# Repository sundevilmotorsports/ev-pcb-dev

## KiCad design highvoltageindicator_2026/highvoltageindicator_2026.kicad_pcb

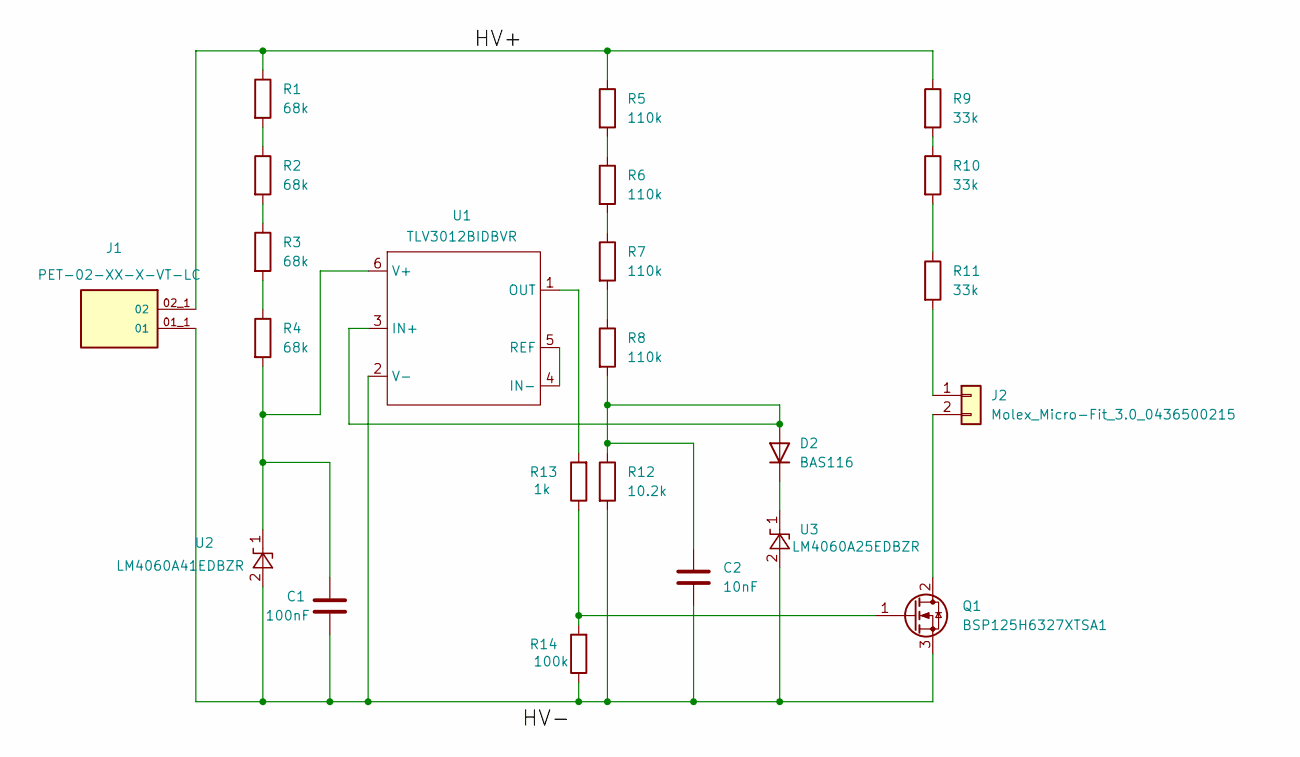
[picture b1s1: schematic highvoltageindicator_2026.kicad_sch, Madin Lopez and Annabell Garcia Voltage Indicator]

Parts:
C1: 100nF; C_1206_3216Metric
C2: 10nF; C_1206_3216Metric
D2: BAS116; SOT-23
J1: PET-02-XX-X-VT-LC; SAMTEC_PET-02-XX-X-VT-LC; PARTREV C
J2: Molex_Micro-Fit_3.0_0436500215; Molex_Micro-Fit_3.0_43650-0215_1x02_P3.00mm_Vertical
Q1: BSP125H6327XTSA1; SOT-223-3_TabPin2
R1, R2, R3, R4: 68k; R_2512_6332Metric
R5, R6, R7, R8: 110k; R_1206_3216Metric
R9, R10, R11: 33k; R_2512_6332Metric
R12: 10.2k; R_1206_3216Metric
R13: 1k; R_1206_3216Metric
R14: 100k; R_1206_3216Metric
U1: TLV3012BIDBVR; SOT-23-6
U2: LM4060A41EDBZR; SOT-23
U3: LM4060A25EDBZR; SOT-23

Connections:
/HV+: J1.02_1 (02), R1.1, R5.1, R9.1
unnamed: C2.1, D2.2 (A), R8.2, R12.1, U1.3 (IN+)
unnamed: D2.1 (K), U3.1 (K)
unnamed: C1.2, C2.2, J1.01_1 (01), Q1.3 (S), R12.2, R14.1, U1.2 (V-), U2.2 (A), U3.2 (A)
unnamed: J2.1, R11.2
unnamed: J2.2, Q1.2 (D)
unnamed: Q1.1 (G), R13.1, R14.2
unnamed: R1.2, R2.1
unnamed: R2.2, R3.1
unnamed: R3.2, R4.1
unnamed: R5.2, R6.1
unnamed: R6.2, R7.1
unnamed: R7.2, R8.1
unnamed: R9.2, R10.1
unnamed: R10.2, R11.1
unnamed: U1.4 (IN-), U1.5 (REF)
unnamed: R13.2, U1.1 (OUT)
unnamed: C1.1, R4.2, U1.6 (V+), U2.1 (K)

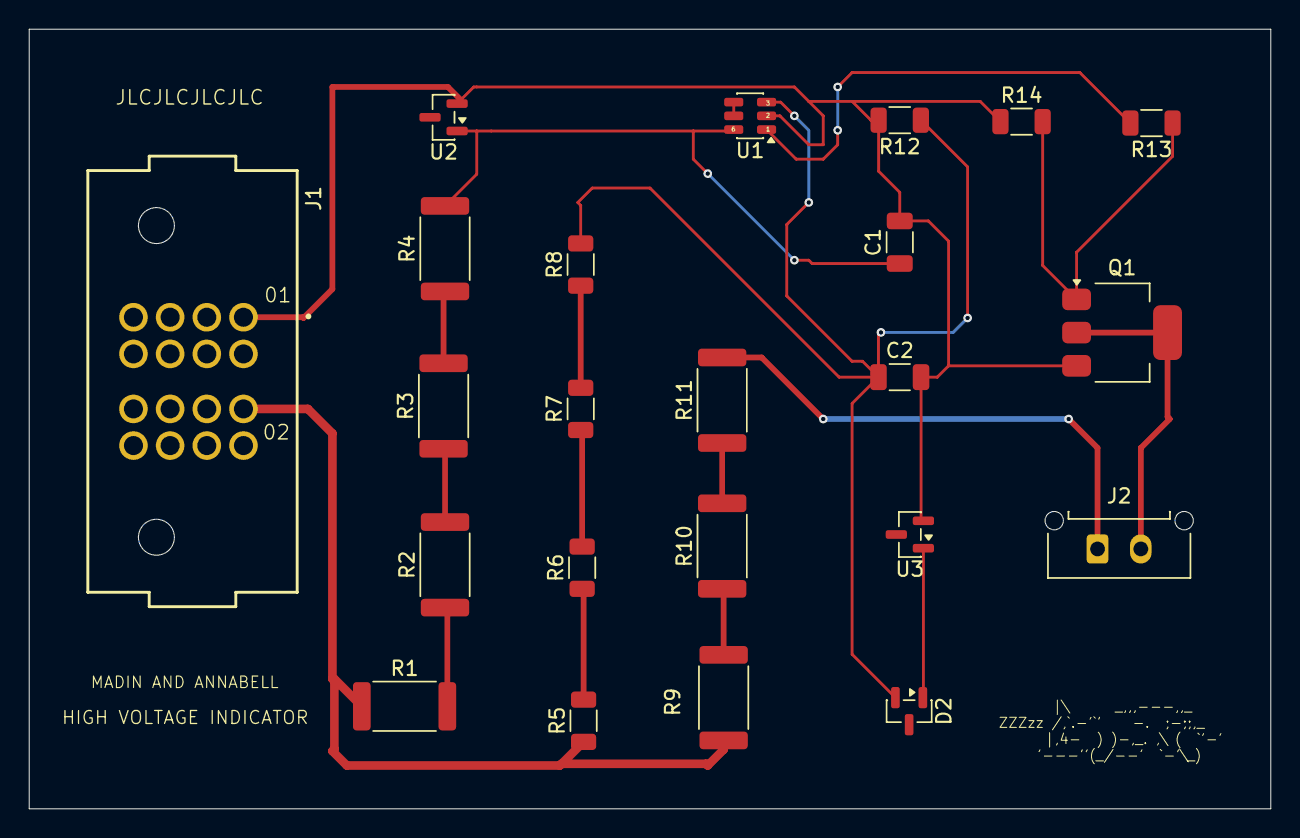
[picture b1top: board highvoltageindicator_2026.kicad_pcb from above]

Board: 4 copper layers, 86.0 x 54.0 mm, 23 parts (0 on the bottom side), 18 nets.

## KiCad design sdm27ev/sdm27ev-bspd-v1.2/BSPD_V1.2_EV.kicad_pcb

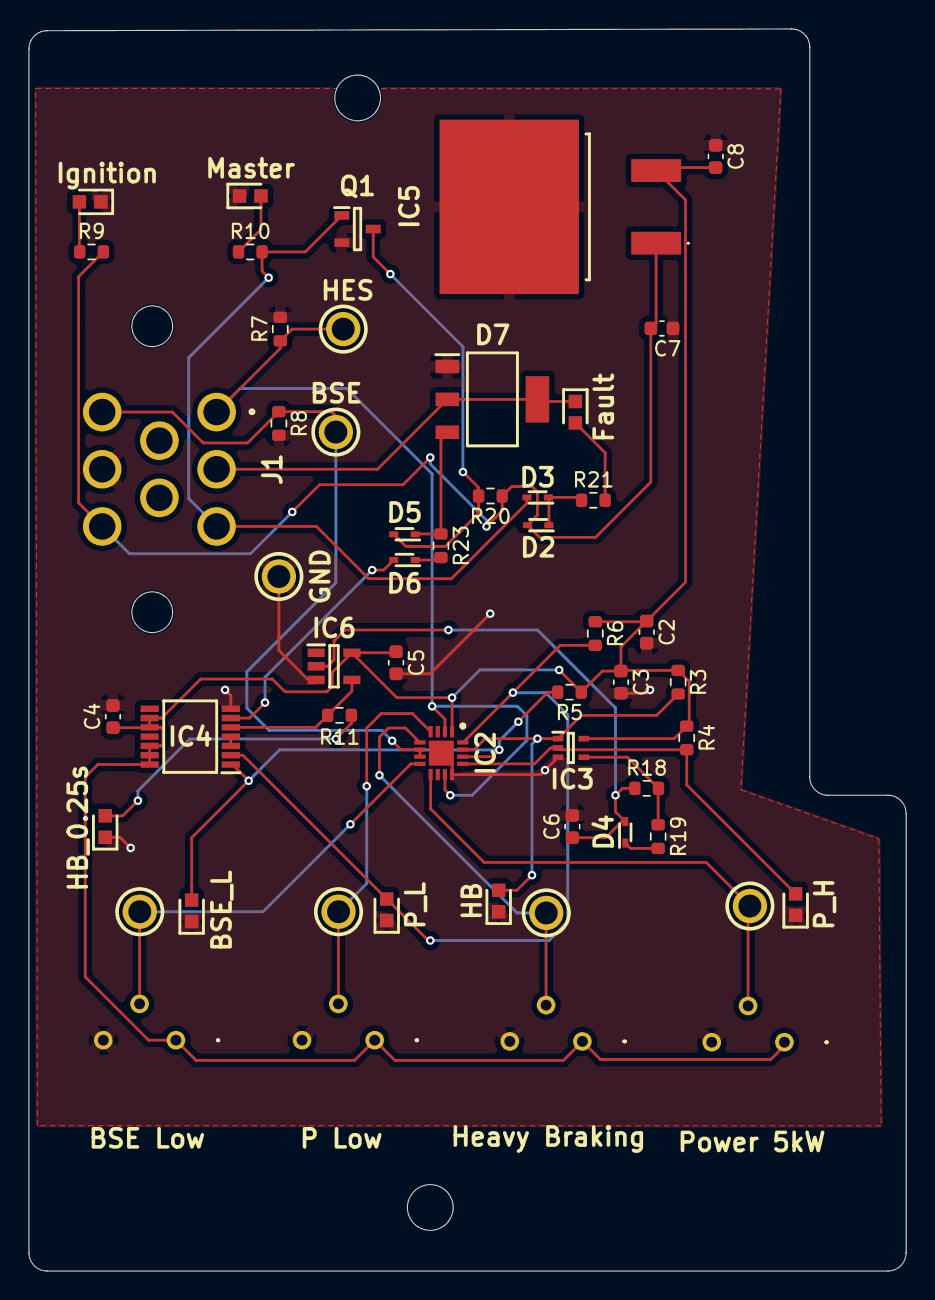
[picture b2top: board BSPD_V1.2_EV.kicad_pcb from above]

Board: 2 copper layers, 61.3 x 86.9 mm, 53 parts (0 on the bottom side), 29 nets.

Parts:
BLACK_TP1: 5006
BSE_L: 150060GS75000; LEDC1608X80N
C2, C3, C4, C5: 1uF; C_0603_1608Metric
C6: 10uF; C_0603_1608Metric
C7: 0.33uF; C_0603_1608Metric
C8: 0.1uF; C_0603_1608Metric
D2, D3, D4, D5, D6: BAT54XV2T1G; SODFL1608X70N
D7: X0202MN_5BA4; SOT230P700X190-4N
Fault: 150060GS75000; LEDC1608X80N
HB: 150060GS75000; LEDC1608X80N
HB_0.25s: 150060GS75000; LEDC1608X80N
IC2: LM2901BIRTER; QFN50P300X300X80-17N-D
IC3: 74AHC1G08; SOT65P212X110-5L
IC4: SN74HC32PWR; SOP65P640X120-14L
IC5: L7805ACD2T-TR; L7805ACD2TTR
IC6: SN74LVC1G17DBVRG4; SOT95P280X145-5N
Ignition: 150060RS75000; LEDC1608X80N
J1: 776280-1
Master: 150060RS75000; LEDC1608X80N
P_H: 150060GS75000; LEDC1608X80N
P_L: 150060GS75000; LEDC1608X80N
Q1: 2N7002,215; SOT95P230X110-3N
R3, R4, R5, R6, R11: 220; R_0603_1608Metric
R7, R8, R20: 10k; R_0603_1608Metric
R9, R10, R21: 510; R_0603_1608Metric
R18: 25k; R_0603_1608Metric
R19: 100; R_0603_1608Metric
R23: 1k; R_0603_1608Metric
RED_TP3, RED_TP4, RED_TP5, RED_TP6: 5005
VR3, VR4, VR5, VR6: 10k; 3386P1103TLF
WHITE_TP1, WHITE_TP2: 5007

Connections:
+5V: C2.1, C3.1, C4.1, C5.1, C8.2, IC2.1 (VCC), IC3.5 (VCC), IC4.9 (3A), IC4.10 (3B), IC4.12 (4A), IC4.13 (4B), IC4.14 (VCC), IC5.3 (OUT), IC6.5 (VCC), R3.1, R4.1, R5.1, R6.1, VR3.1 (CCW), VR4.1 (CCW), VR5.1 (CCW), VR6.1 (CCW)
/12V IGNITION: C7.2, D2.2 (A), IC5.1 (IN), J1.8, R9.2, R20.1
/12V MASTER: D3.2 (A), J1.3, Q1.1 (G), R10.2
/BL+PL_FAULT: IC4.3 (1Y), IC4.4 (2A)
/BSE: IC2.6 (IN2+), IC2.7 (IN3-), J1.6, R8.1, WHITE_TP1.1
/BSE_LOW_FAULT: BSE_L.2 (A), IC2.14 (OUT3), IC4.1 (1A), R5.2
/BSE_LOW_REF: IC2.8 (IN3+), RED_TP6.1, VR6.2 (Wiper)
/BSPD_LOGIC_SIGNAL: D6.2 (A), IC4.6 (2Y)
/HB*5kW_0.25s_FAULT: IC4.5 (2B), IC6.4 (Y), R11.1
/HB*5kW_FAULT: C6.1, D4.2 (A), IC6.2 (A), R18.2
/HEAVY_BRAKING_FAULT: HB.2 (A), IC2.15 (OUT2), IC3.1 (B), R3.2
/HEAVY_BRAKING_REF: IC2.5 (IN2-), RED_TP4.1, VR4.2 (Wiper)
/P_5kW_FAULT: IC2.13 (OUT4), IC3.2 (A), P_H.2 (A), R4.2
/P_HIGH_REF: IC2.9 (IN4-), RED_TP3.1, VR3.2 (Wiper)
/P_LOW_FAULT: IC2.16 (OUT1), IC4.2 (1B), P_L.2 (A), R6.2
/P_LOW_REF: IC2.4 (IN1+), RED_TP5.1, VR5.2 (Wiper)
/P_MAIN: IC2.2 (IN1-), IC2.11 (IN4+), J1.1, R7.1, WHITE_TP2.1
/SCR Gate: D5.1 (K), D7.3 (G), R23.1
BSPD KILL SIGNAL: D7.2 (A_1), D7.4 (A_2), Fault.1 (K), J1.2
GND: BLACK_TP1.1, BSE_L.1 (K), C2.2, C3.2, C4.2, C5.2, C6.2, C7.1, C8.1, D7.1 (K), HB.1 (K), HB_0.25s.1 (K), IC2.12 (GND), IC2.17 (EP), IC3.3 (GND), IC4.7 (GND), IC5.2 (GND), IC6.3 (GND), Ignition.1 (K), J1.7, Master.1 (K), P_H.1 (K), P_L.1 (K), Q1.2 (S), R7.2, R8.2, VR3.3 (CW), VR4.3 (CW), VR5.3 (CW), VR6.3 (CW)
unnamed: D2.1 (K), D3.1 (K), R21.1
unnamed: D4.1 (K), R19.2
unnamed: D5.2 (A), Q1.3 (D), R20.2
unnamed: D6.1 (K), R23.2
unnamed: IC3.4 (Y), R18.1, R19.1
unnamed: Ignition.2 (A), R9.1
unnamed: Master.2 (A), R10.1
unnamed: Fault.2 (A), R21.2
unnamed: HB_0.25s.2 (A), R11.2

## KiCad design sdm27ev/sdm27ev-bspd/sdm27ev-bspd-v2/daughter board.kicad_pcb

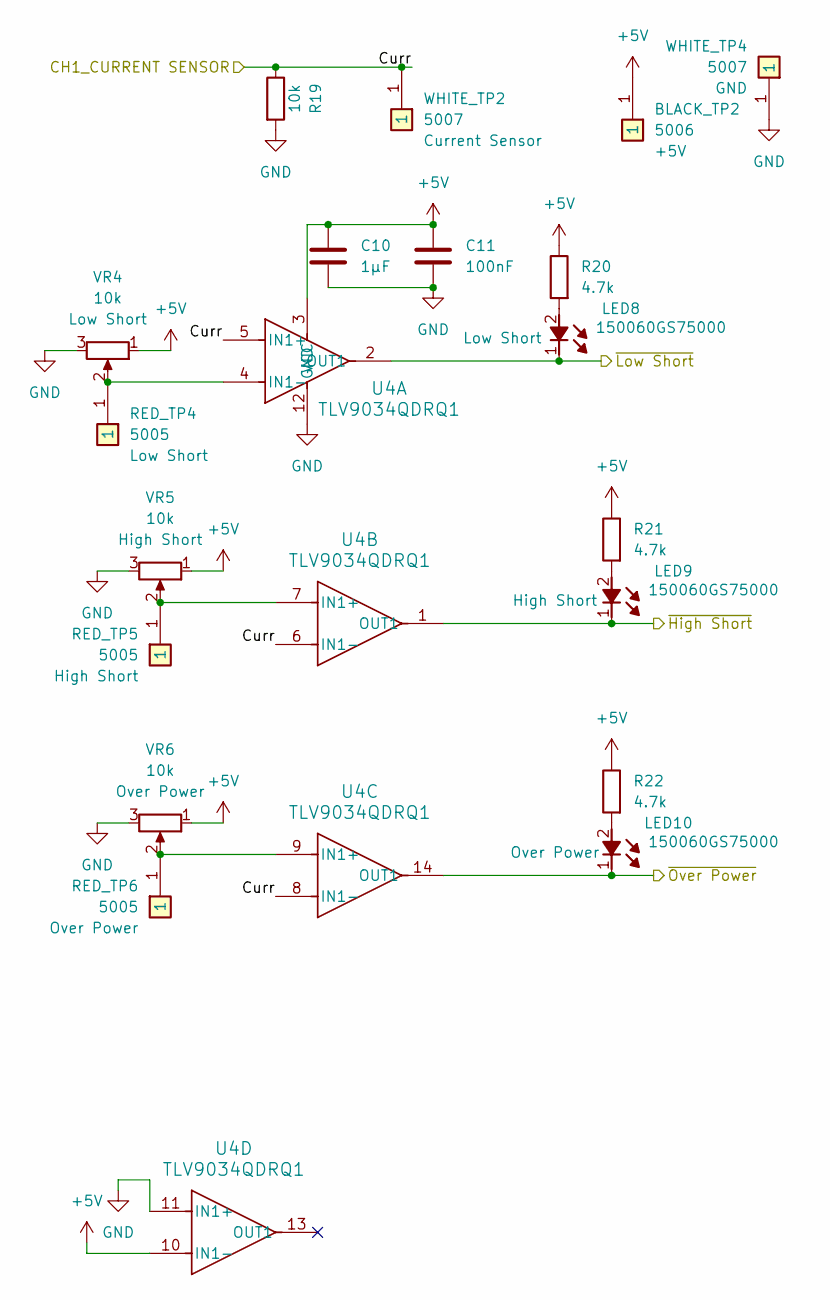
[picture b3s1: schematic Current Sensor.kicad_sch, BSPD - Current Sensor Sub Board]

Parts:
BLACK_TP2: 5006; Mouser Part Number 534-5006
C10: 1µF; C_0603_1608Metric
C11: 100nF; C_0603_1608Metric
LED8, LED9, LED10: 150060GS75000; LEDC1608X80N; Mouser Part Number 710-150060GS75000
R19: 10k; R_0603_1608Metric
R20, R21, R22: 4.7k; R_0603_1608Metric
RED_TP4, RED_TP5, RED_TP6: 5005; Mouser Part Number 534-5005
U4: TLV9034QDRQ1; SOIC-14_3.9x8.7mm_P1.27mm; Manufacturer_Part_Number TLV9034QDRQ1; Mouser Part Number 595-TLV9034QDRQ1
VR4, VR5, VR6: 10k; 3386P1103TLF; Mouser Part Number 652-3386P-1-103TLF
WHITE_TP2, WHITE_TP4: 5007; Mouser Part Number 534-5007

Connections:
+5V: BLACK_TP2.1 (1_1), C10.1, C11.1, R20.1, R21.1, R22.1, U4.3 (VCC), U4.10 (IN1-), VR4.1 (CCW), VR5.1 (CCW), VR6.1 (CCW); also elsewhere on the board
/CH1_CURRENT SENSOR: R19.1, U4.5 (IN1+), U4.6 (IN1-), U4.8 (IN1-), WHITE_TP2.1 (1_1); also elsewhere on the board
/~High Short: LED9.1 (K), U4.1 (OUT1); also elsewhere on the board
/~Low Short: LED8.1 (K), U4.2 (OUT1); also elsewhere on the board
/~Over Power: LED10.1 (K), U4.14 (OUT1); also elsewhere on the board
GND: C10.2, C11.2, R19.2, U4.11 (IN1+), U4.12 (GND), VR4.3 (CW), VR5.3 (CW), VR6.3 (CW), WHITE_TP4.1 (1_1); also elsewhere on the board
unnamed: LED8.2 (A), R20.2
unnamed: LED9.2 (A), R21.2
unnamed: LED10.2 (A), R22.2
unnamed: RED_TP4.1 (1_1), U4.4 (IN1-), VR4.2 (Wiper)
unnamed: RED_TP5.1 (1_1), U4.7 (IN1+), VR5.2 (Wiper)
unnamed: RED_TP6.1 (1_1), U4.9 (IN1+), VR6.2 (Wiper)

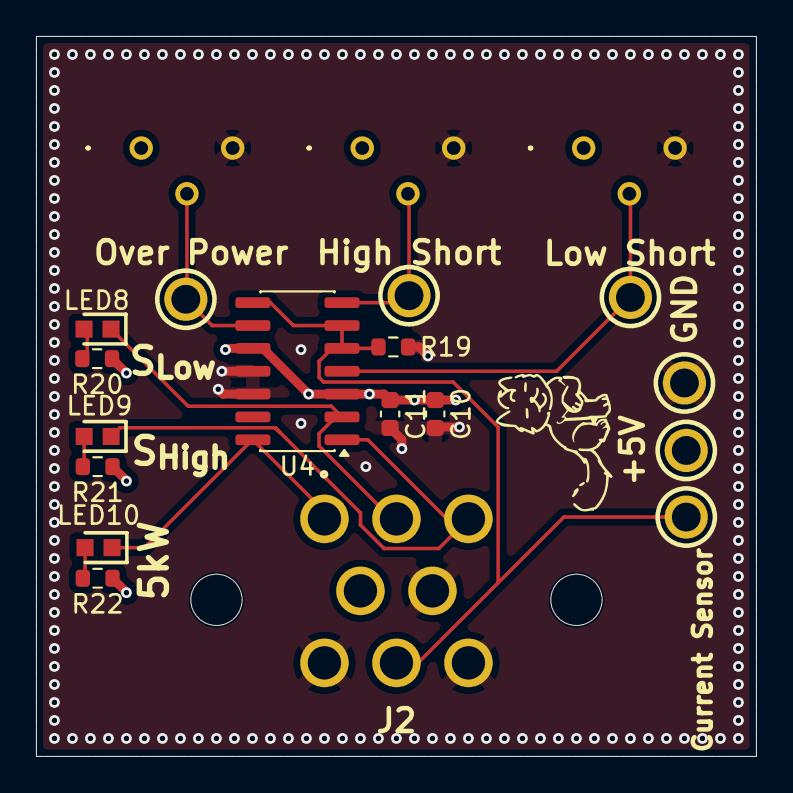
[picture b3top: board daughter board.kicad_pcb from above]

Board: 4 copper layers, 40.0 x 40.0 mm, 20 parts (0 on the bottom side), 12 nets.

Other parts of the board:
J2: 776280-1

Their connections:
+5V: J2.4; also elsewhere on the board
/CH1_CURRENT SENSOR: J2.7; also elsewhere on the board
/~High Short: J2.3; also elsewhere on the board
/~Low Short: J2.2; also elsewhere on the board
/~Over Power: J2.1; also elsewhere on the board
GND: J2.5, J2.6, J2.8; also elsewhere on the board

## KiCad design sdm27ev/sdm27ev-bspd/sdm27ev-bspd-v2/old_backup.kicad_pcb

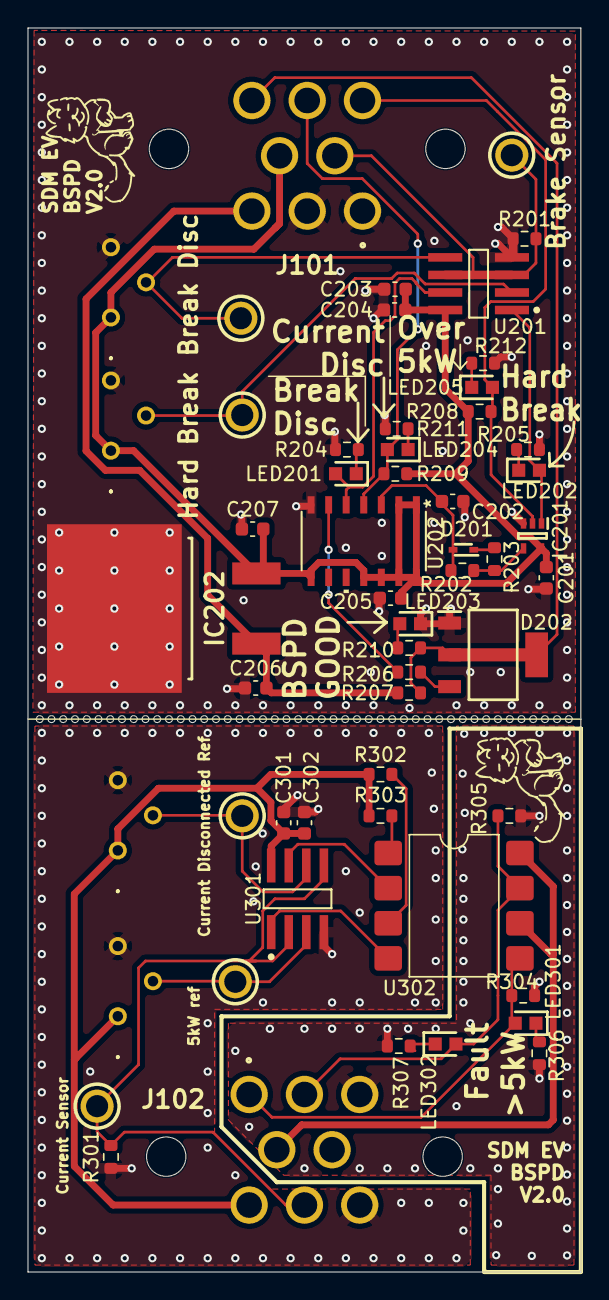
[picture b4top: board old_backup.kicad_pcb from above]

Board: 2 copper layers, 40.0 x 90.0 mm, 57 parts (0 on the bottom side), 32 nets.

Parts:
C201, C203, C301: 1µF; C_0603_1608Metric
C202: 10µF; C_0603_1608Metric
C204, C205, C302: 100nF; C_0603_1608Metric
C206: 0.33µF; C_0603_1608Metric
C207: 0.1µF; C_0603_1608Metric
D201: BAT54XV2T1G; SODFL1608X70N
D202: X0202MN_5BA4; SOT230P700X190-4N
Dylan Shah: LOGO; Robocat 10x10mm
Dylan Shah#2: LOGO; Robocat 10x10mm
IC201: 74AHC1G08GW,125; SOT65P212X110-5L
IC202: L7805ACD2T-TR; L7805ACD2TTR
J101, J102: 776280-1
LED201, LED202, LED203, LED204, LED205, LED301, LED302: 150060GS75000; LEDC1608X80N
R201, R210, R301, R304, R305: 10k; R_0603_1608Metric
R202: 39k; R_0603_1608Metric
R203: 100; R_0603_1608Metric
R204, R205, R206, R211, R212, R306, R307: 4.7k; R_0603_1608Metric
R207: 380; R_0603_1608Metric
R208, R209: 100k; R_0603_1608Metric
R302, R303: 680; R_0603_1608Metric
RED_TP201, RED_TP202, RED_TP301, RED_TP302: 5005
U201, U301: TLV9032QDRQ1; TLV9032QDRQ1-IPC_A
U202: SN74HCS4075DR
U302: LTV-827S; SMDIP-8_W9.53mm
VR201, VR202, VR301, VR302: 10k; 3386P1103TLF
WHITE_TP201, WHITE_TP301: 5007

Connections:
+5V: C201.1, C203.1, C204.1, C205.2, C207.2, IC201.5 (VCC), IC202.3 (OUT), J101.5, J102.4, R208.2, R209.2, U201.8 (VCC), U202.1 (2A), U202.2 (2B), U202.8 (2C), U202.11 (3A), U202.12 (3B), U202.13 (3C), U202.14 (VCC), U302.6, U302.8, VR201.1 (CCW), VR202.1 (CCW)
+5V_BMS: C301.1, C302.1, J102.6, R302.1, R303.2, U301.8 (VCC), VR301.1 (CCW), VR302.1 (CCW)
+12V: C206.2, IC202.1 (IN), J101.3, R207.1
/CH1_CURRENT SENSOR: J102.7, R301.2, U301.2 (IN1-), U301.5 (IN2+), WHITE_TP301.1 (1_1)
/Current Sensor Fault: J101.7, J102.2, LED204.2 (A), LED302.2 (A), R209.1, R305.1, U202.4 (1B), U302.7
/Current Sensor Sub-Board/Over Current Ref: RED_TP301.1 (1_1), U301.3 (IN1+), VR301.2 (Wiper)
/Current Sensor Sub-Board/Under Current Ref: RED_TP302.1 (1_1), U301.6 (IN2-), VR302.2 (Wiper)
/Current Sensor Sub-Board/~Current Sensor Fault: U301.7 (OUT2), U302.2
/Current Sensor Sub-Board/~Over Current Fault: U301.1 (OUT1), U302.4
/Main Board/Brake Connection Fault Ref: RED_TP202.1 (1_1), U201.5 (IN2+), VR202.2 (Wiper)
/Main Board/Brake Sensor: J101.4, R201.2, U201.3 (IN1+), U201.6 (IN2-), WHITE_TP201.1 (1_1)
/Main Board/Break Disconnected: LED201.2 (A), U201.7 (OUT2), U202.5 (1C)
/Main Board/Combined Fault Line: R206.1, U202.6 (1Y)
/Main Board/Hard Breaking: IC201.1 (B), LED202.2 (A), U201.1 (OUT1)
/Main Board/Over power and break for 0.25s: C202.1, D201.2 (A), R202.2, U202.3 (1A)
/Main Board/~BSPD Fault: D202.2 (A_1), D202.4 (A_2), J101.8 (Pin_2), R207.2, R210.1
/POWER OVER FAUT: IC201.2 (A), J101.6, J102.1, LED205.2 (A), LED301.2 (A), R208.1, R304.2, U302.5
GND: C201.2, C202.2, C203.2, C204.2, C205.1, C206.1, C207.1, D202.1 (K), IC201.3 (GND), IC202.2 (GND), J101.1, J101.2 (Pin_8), J102.3, LED203.1 (K), R201.1, R204.2, R205.2, R211.2, R212.2, R304.1, R305.2, R306.2, R307.2, U201.4 (GND), U202.7 (GND), VR201.3 (CW), VR202.3 (CW)
GND_BMS: C301.2, C302.2, J102.8, R301.1, U301.4 (GND), VR301.3 (CW), VR302.3 (CW)
unnamed: D201.1 (K), R203.2
unnamed: D202.3 (G), R206.2
unnamed: IC201.4 (Y), R202.1, R203.1
unnamed: LED201.1 (K), R204.1
unnamed: LED202.1 (K), R205.1
unnamed: LED203.2 (A), R210.2
unnamed: LED204.1 (K), R211.1
unnamed: LED205.1 (K), R212.1
unnamed: LED301.1 (K), R306.1
unnamed: LED302.1 (K), R307.1
unnamed: R302.2, U302.3
unnamed: R303.1, U302.1
unnamed: RED_TP201.1 (1_1), U201.2 (IN1-), VR201.2 (Wiper)

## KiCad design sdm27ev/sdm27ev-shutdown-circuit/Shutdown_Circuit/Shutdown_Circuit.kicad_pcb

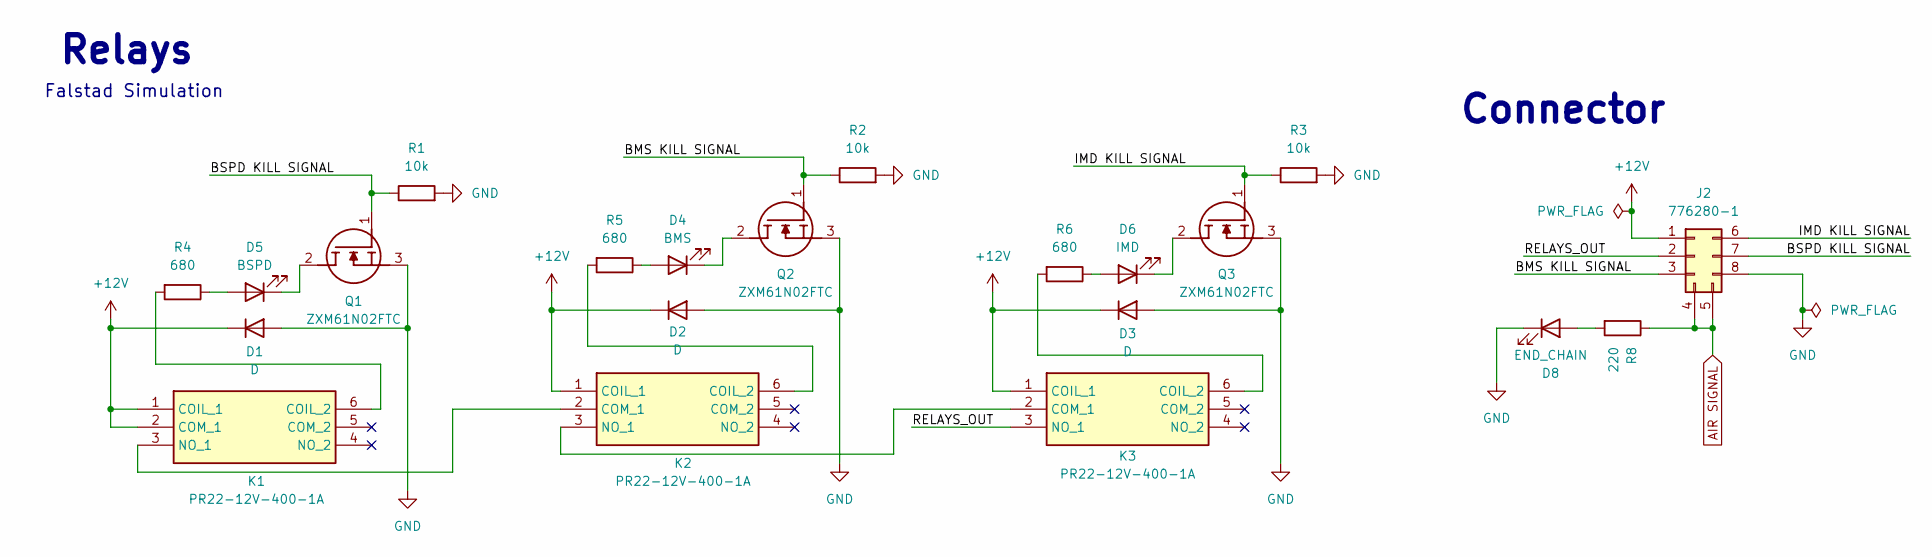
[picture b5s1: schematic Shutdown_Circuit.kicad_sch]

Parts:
D1, D2, D3: D; SODFL1608X70N
D4: BMS; LED_0603_1608Metric
D5: BSPD; LED_0603_1608Metric
D6: IMD; LED_0603_1608Metric
D8: END_CHAIN; LED_0603_1608Metric
J2: 776280-1; Mouser Part Number 571-776280-1
K1, K2, K3: PR22-12V-400-1A; PR2212V4001A; Mouser Part Number 655-V23047A1012A511
Q1, Q2, Q3: ZXM61N02FTC; Manufacturer_Part_Number ZXM61N02FTC; Mouser Part Number 522-ZXM61N02FTC
R1, R2, R3: 10k; R_0603_1608Metric
R4, R5, R6: 680; R_0603_1608Metric
R8: 220; R_0603_1608Metric

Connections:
+12V: D1.1 (K), D2.1 (K), D3.1 (K), J2.1, K1.1 (COIL_1), K1.2 (COM_1), K2.1 (COIL_1), K3.1 (COIL_1)
/BMS KILL SIGNAL: J2.3, Q2.1 (G), R2.1
/BSPD KILL SIGNAL: J2.7, Q1.1 (G), R1.1
/IMD KILL SIGNAL: J2.6, Q3.1 (G), R3.1
/RELAYS_OUT: J2.2, K3.3 (NO_1)
AIR SIGNAL: J2.4, J2.5, R8.1
GND: D1.2 (A), D2.2 (A), D3.2 (A), D8.1 (K), J2.8, Q1.3 (S), Q2.3 (S), Q3.3 (S), R1.2, R2.2, R3.2
unnamed: D4.2 (A), R5.1
unnamed: D4.1 (K), Q2.2 (D)
unnamed: D5.2 (A), R4.1
unnamed: D5.1 (K), Q1.2 (D)
unnamed: D6.2 (A), R6.1
unnamed: D6.1 (K), Q3.2 (D)
unnamed: D8.2 (A), R8.2
unnamed: K1.6 (COIL_2), R4.2
unnamed: K1.3 (NO_1), K2.2 (COM_1)
unnamed: K2.6 (COIL_2), R5.2
unnamed: K2.3 (NO_1), K3.2 (COM_1)
unnamed: K3.6 (COIL_2), R6.2

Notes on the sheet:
Falstad Simulation
Connector
Relays

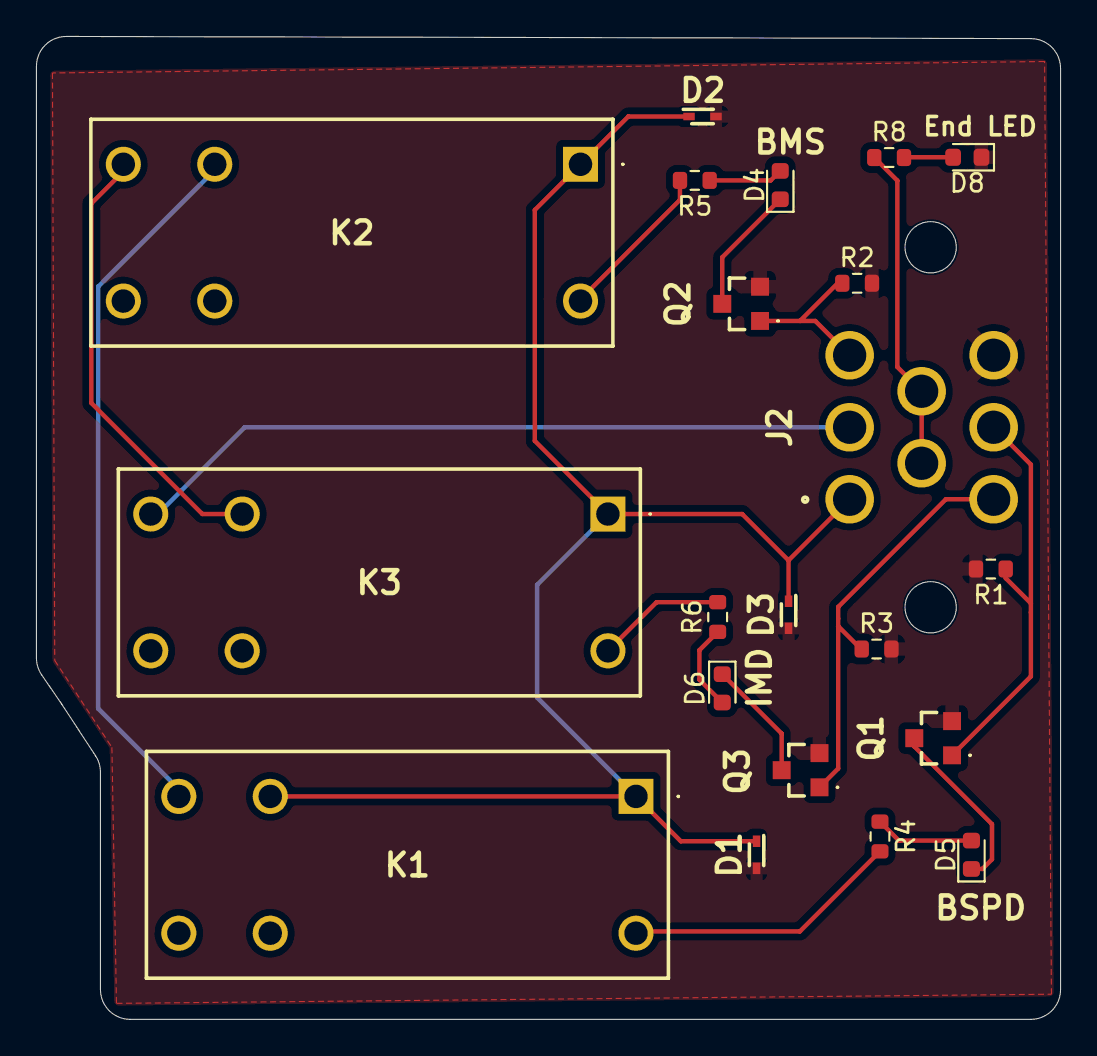
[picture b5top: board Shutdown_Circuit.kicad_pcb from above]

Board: 2 copper layers, 56.9 x 54.6 mm, 21 parts (0 on the bottom side), 19 nets.

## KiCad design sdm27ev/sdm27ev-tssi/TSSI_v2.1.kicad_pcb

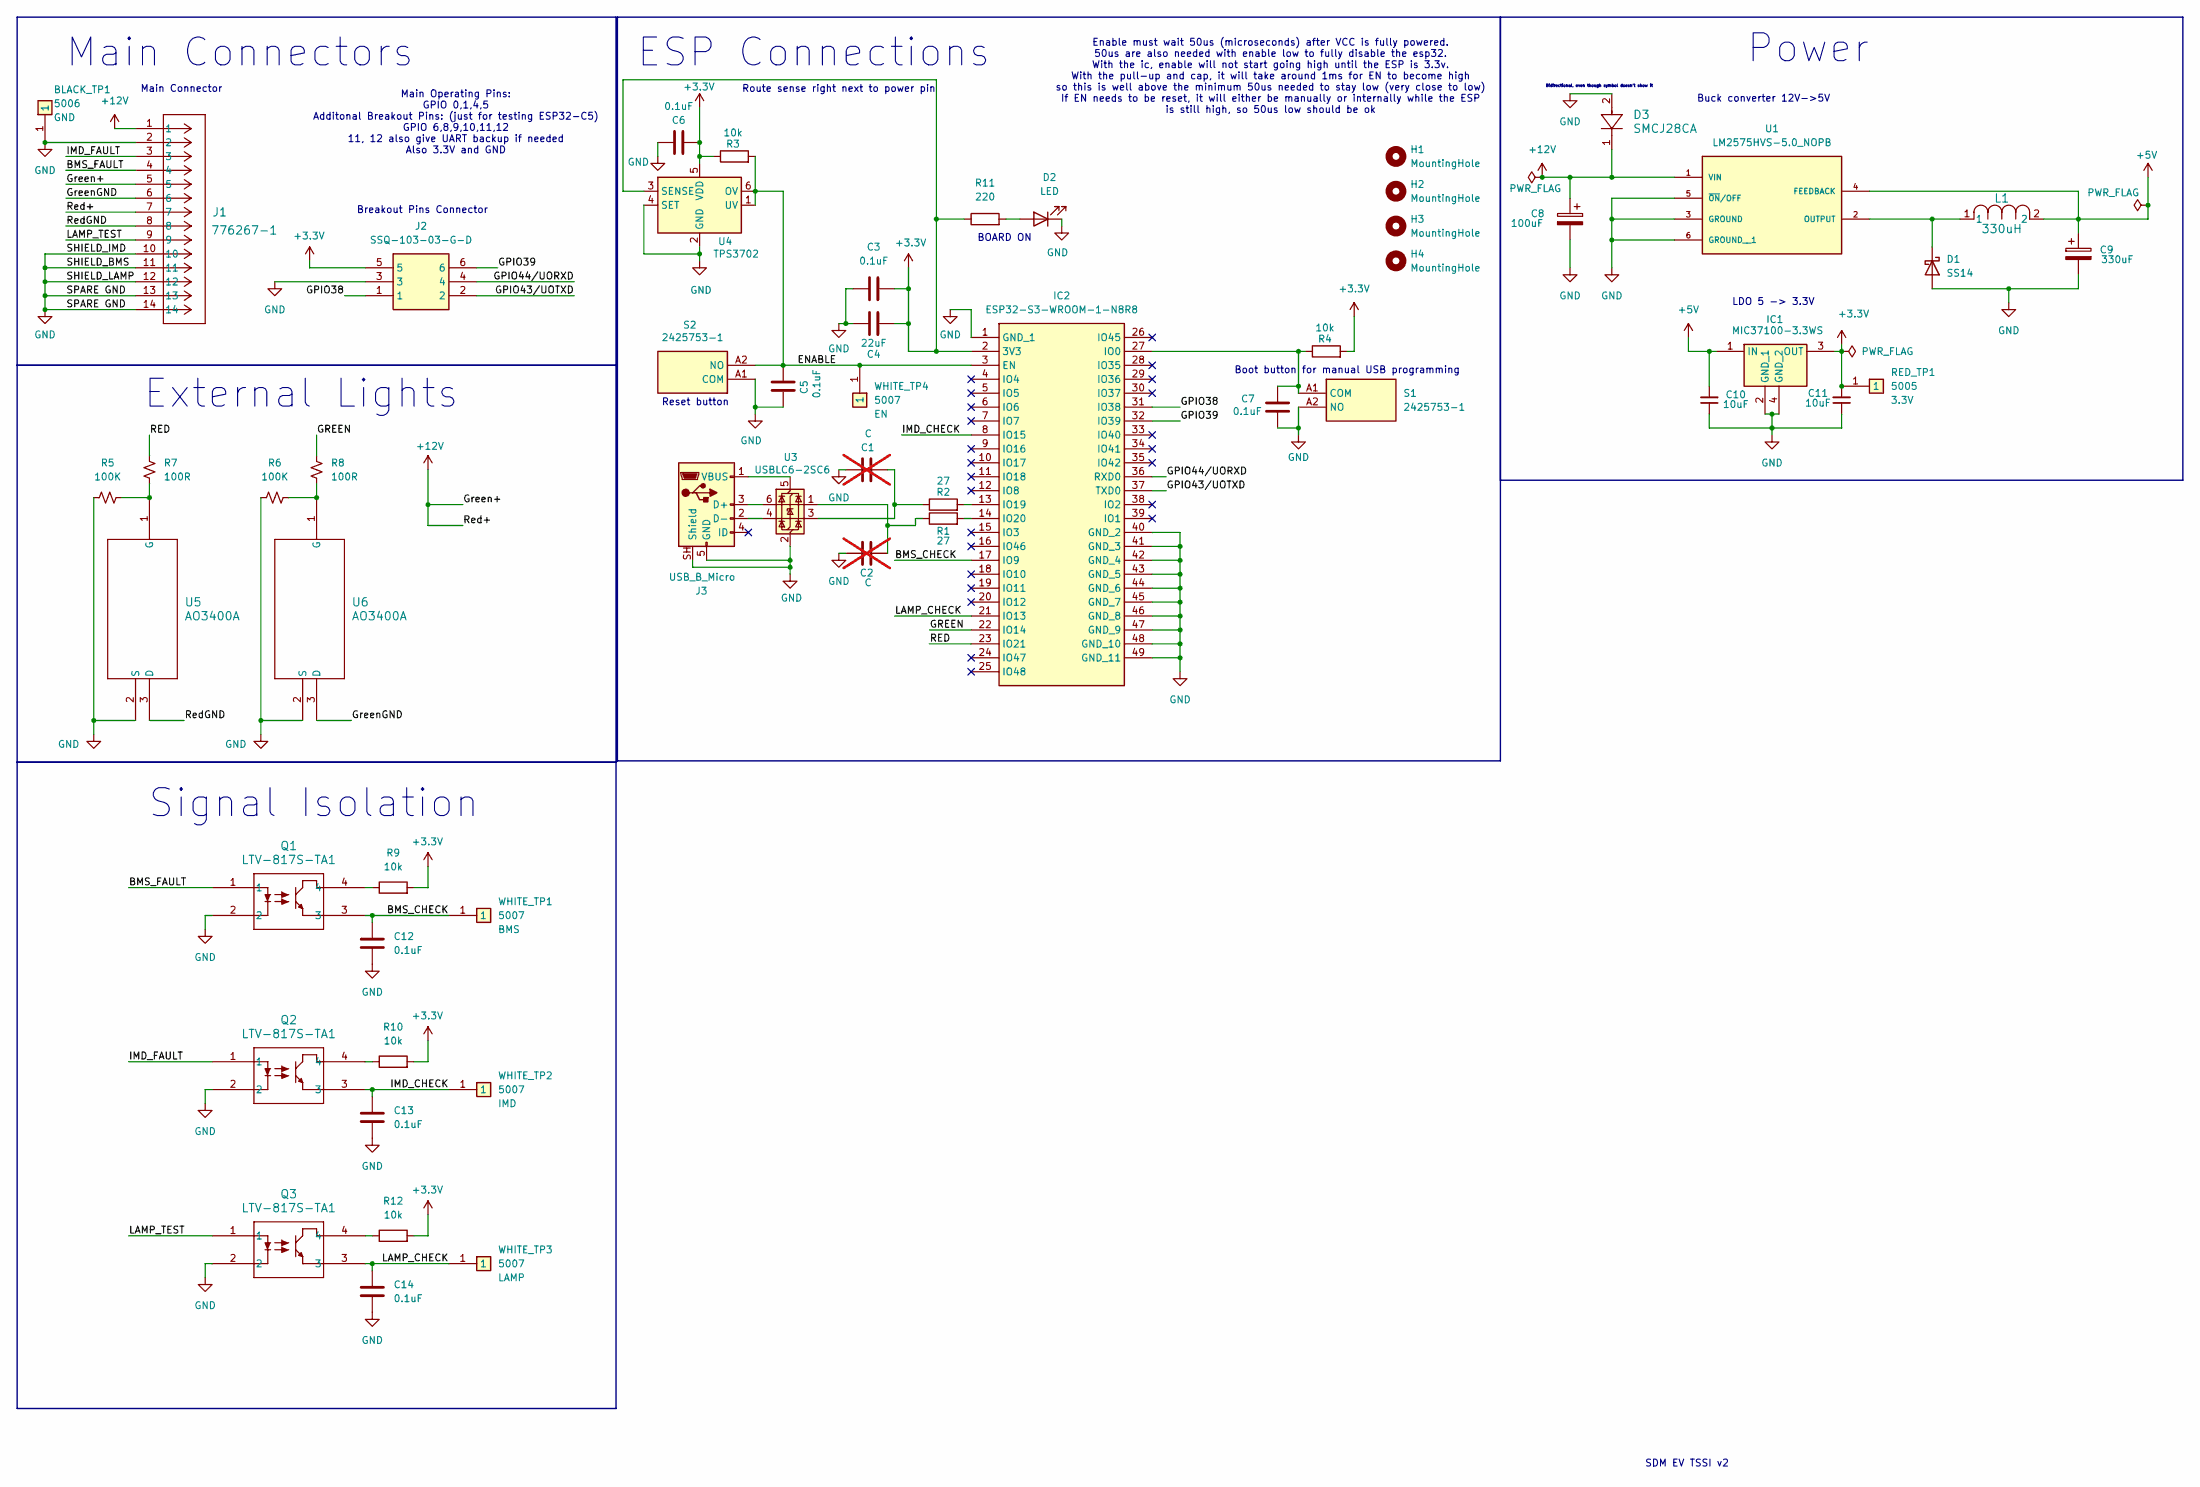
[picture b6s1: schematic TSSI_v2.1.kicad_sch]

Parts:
BLACK_TP1: 5006; Mouser Part Number 534-5006
C1, C2: C; C_0603_1608Metric; not fitted
C3, C5, C6, C7, C12, C13, C14: 0.1uF; C_0603_1608Metric
C4: 22uF; C_0603_1608Metric
C8: 100uF; WCAP-ASLI_6.3X7.7_DXL_
C9: 330uF; CP_Elec_10x10
C10, C11: 10uF; C_0603_1608Metric
D1: SS14; D_SMA
D2: LED; LED_0603_1608Metric
D3: SMCJ28CA; SMCJSeries_LTF
H1, H2, H3, H4: MountingHole; MountingHole_2.2mm_M2
IC1: MIC37100-3.3WS; SOT-223; Mouser Part Number 998-MIC37100-3.3WS
IC2: ESP32-S3-WROOM-1-N8R8; XCVR_ESP32S3WROOM1N8R8; Mouser Part Number 356-EP32S3WROOM1N8R8
J1: 776267-1; CONN14_776267_TEC
J2: SSQ-103-03-G-D; SSQ-103-XX-YYY-D; Mouser Part Number 200-SSQ10303GD
J3: USB_B_Micro; USB_Micro-B_Molex-105017-0001
L1: 330uH; IND_SPD127R_API
Q1, Q2, Q3: LTV-817S-TA1; LTV-817S_LTO
R1, R2: 27; R_0603_1608Metric
R3, R4, R9, R10, R12: 10k; R_0603_1608Metric
R5, R6: 100K; R_0603_1608Metric_Pad0.98x0.95mm_HandSolder
R7, R8: 100R; R_0603_1608Metric_Pad0.98x0.95mm_HandSolder
R11: 220; R_0603_1608Metric
RED_TP1: 5005; Mouser Part Number 534-5005
S1, S2: 2425753-1; 24257531; Mouser Part Number 655-2425753-1
U1: LM2575HVS-5.0_NOPB; VREG_LM2575HVS-5.0_NOPB; PARTREV E
U3: USBLC6-2SC6; SOT-23-6
U4: TPS3702; SOT-23-6
U5, U6: AO3400A; SOT-23-3L_AOS
WHITE_TP1, WHITE_TP2, WHITE_TP3, WHITE_TP4: 5007; Mouser Part Number 534-5007

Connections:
+3.3V: C3.2, C4.2, C6.1, C11.2, IC1.3 (OUT), IC2.2 (3V3), J2.5, R3.1, R4.2, R9.2, R10.2, R11.1, R12.2, RED_TP1.1 (1_1), U4.3 (SENSE), U4.5 (VDD)
+5V: C9.1, C10.2, IC1.1 (IN), L1.2, U1.4 (FEEDBACK)
+12V: C8.1, D3.1, J1.1, J1.5, J1.7, U1.1 (VIN)
/BMS_CHECK: C12.1, IC2.17 (IO9), Q1.3, WHITE_TP1.1 (1_1)
/BMS_FAULT: J1.4, Q1.1
/ENABLE: C5.1, IC2.3 (EN), R3.2, S2.A2 (NO), U4.1 (UV), U4.6 (OV), WHITE_TP4.1 (1_1)
/GPIO38: IC2.31 (IO38), J2.1
/GPIO39: IC2.32 (IO39), J2.6
/GPIO43/UOTXD: IC2.37 (TXD0), J2.2
/GPIO44/UORXD: IC2.36 (RXD0), J2.4
/GREEN: IC2.22 (IO14), R8.1
/GreenGND: J1.6, U6.3 (D)
/IMD_CHECK: C13.1, IC2.8 (IO15), Q2.3, WHITE_TP2.1 (1_1)
/IMD_FAULT: J1.3, Q2.1
/LAMP_CHECK: C14.1, IC2.21 (IO13), Q3.3, WHITE_TP3.1 (1_1)
/LAMP_TEST: J1.9, Q3.1
/RED: IC2.23 (IO21), R7.1
/RedGND: J1.8, U5.3 (D)
GND: BLACK_TP1.1 (1_1), C1.1, C2.1, C3.1, C4.1, C5.2, C6.2, C7.1, C8.2, C9.2, C10.1, C11.1, C12.2, C13.2, C14.2, D1.2 (A), D2.1 (K), D3.2, IC1.2 (GND_1), IC1.4 (GND_2), IC2.1 (GND_1), IC2.40 (GND_2), IC2.41 (GND_3), IC2.42 (GND_4), IC2.43 (GND_5), IC2.44 (GND_6), IC2.45 (GND_7), IC2.46 (GND_8), IC2.47 (GND_9), IC2.48 (GND_10), IC2.49 (GND_11), J1.2, J1.10, J1.11, J1.12, J1.13, J1.14, J2.3, J3.5 (GND), J3.SH (Shield), Q1.2, Q2.2, Q3.2, R5.1, R6.1, S1.A2 (NO), S2.A1 (COM), U1.3 (GROUND), U1.5 (~ON/OFF), U1.6 (GROUND__1), U3.2 (GND), U4.2 (GND), U4.4 (SET), U5.2 (S), U6.2 (S)
unnamed: C1.2, R2.1, U3.3 (I/O2)
unnamed: C2.2, R1.1, U3.1 (I/O1)
unnamed: D1.1 (K), L1.1, U1.2 (OUTPUT)
unnamed: D2.2 (A), R11.2
unnamed: C7.2, IC2.27 (IO0), R4.1, S1.A1 (COM)
unnamed: IC2.13 (IO19), R2.2
unnamed: IC2.14 (IO20), R1.2
unnamed: J3.3 (D+), U3.6 (I/O1)
unnamed: J3.2 (D-), U3.4 (I/O2)
unnamed: J3.1 (VBUS), U3.5 (VBUS)
unnamed: Q1.4, R9.1
unnamed: Q2.4, R10.1
unnamed: Q3.4, R12.1
unnamed: R5.2, R7.2, U5.1 (G)
unnamed: R6.2, R8.2, U6.1 (G)

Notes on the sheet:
LDO 5 -> 3.3V
SDM EV TSSI v2
Reset button
Buck converter 12V->5V
Bidirectional, even though symbol doesn't show it
Signal Isolation
Main Operating Pins: GPIO 0,1,4,5 Additonal Breakout Pins: (just for testing ESP32-C5) GPIO 6,8,9,10,11,12 11, 12 also give UART backup if needed Also 3.3V and GND
Power
ESP Connections
External Lights
Route sense right next to power pin
Enable must wait 50us (microseconds) after VCC is fully powered. 50us are also needed with enable low to fully disable the esp32. With the ic, enable will not start going high until the ESP is 3.3v. With the pull-up and cap, it will take around 1ms for EN to become high so this is well above the mi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
Main Connector
BOARD ON
Main Connectors
Breakout Pins Connector
Boot button for manual USB programming

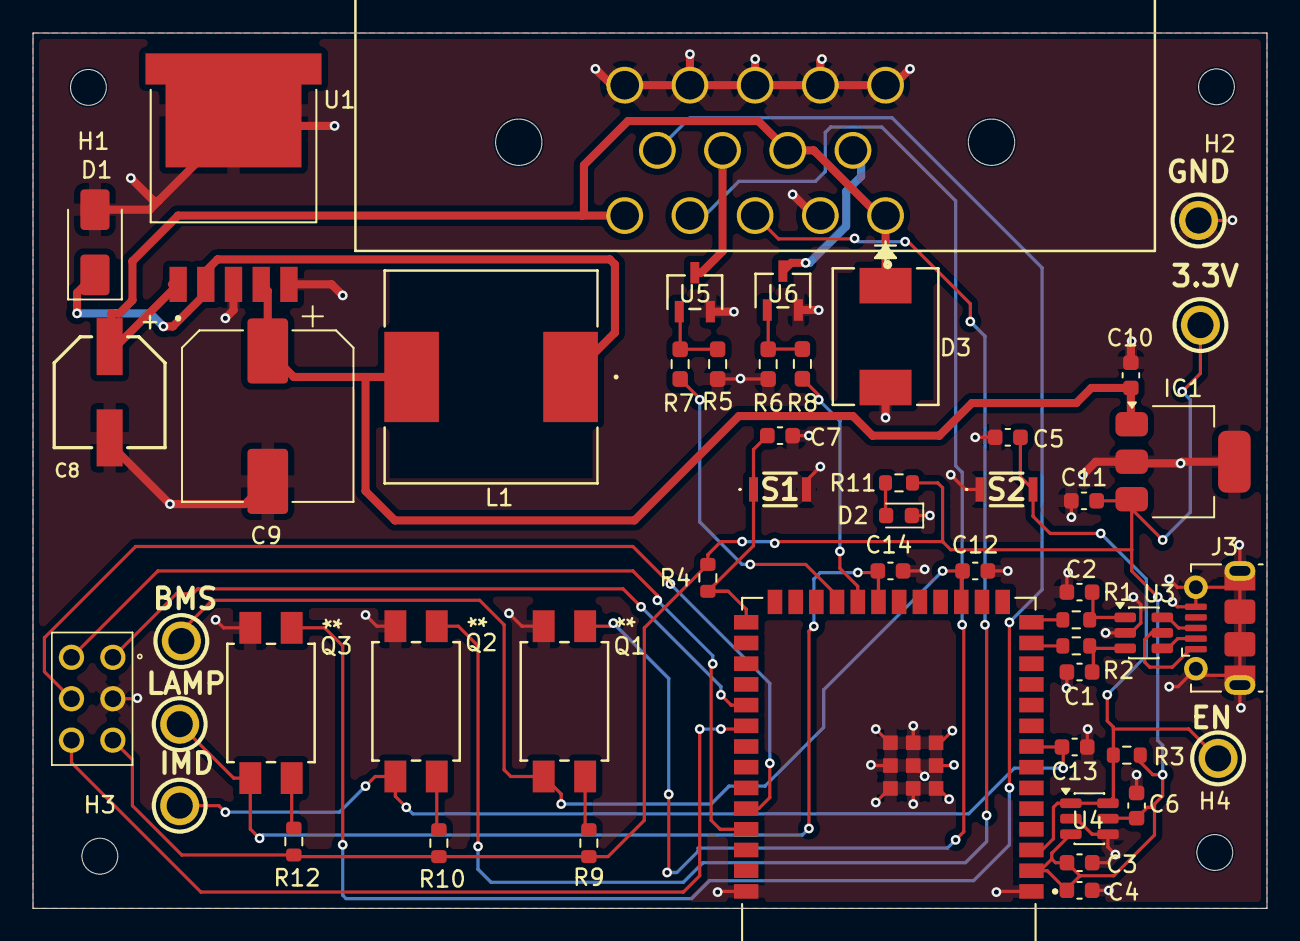
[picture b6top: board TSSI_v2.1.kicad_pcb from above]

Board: 2 copper layers, 75.7 x 53.7 mm, 55 parts (0 on the bottom side), 34 nets.

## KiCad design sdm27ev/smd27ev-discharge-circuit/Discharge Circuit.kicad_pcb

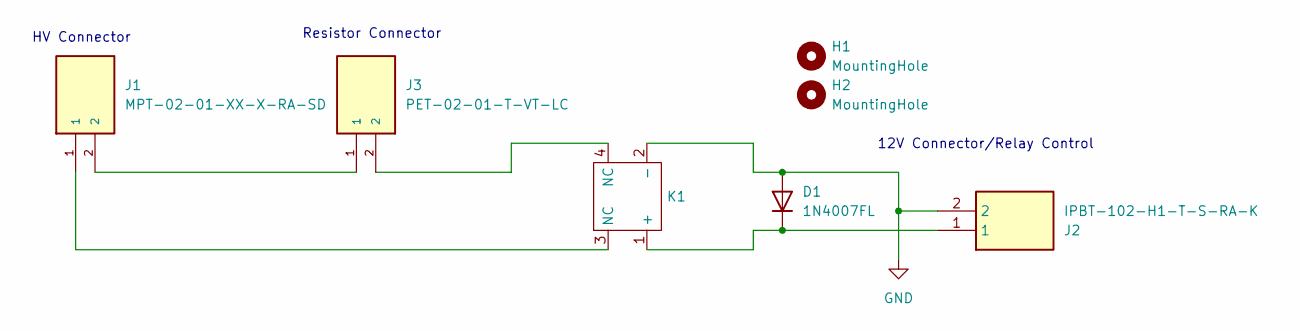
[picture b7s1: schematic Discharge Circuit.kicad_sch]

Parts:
D1: 1N4007FL; D_SOD-123F
H1, H2: MountingHole; MountingHole_3.2mm_M3
J1: MPT-02-01-XX-X-RA-SD; SAMTEC_MPT-02-01-XX-X-RA-SD; PARTREV B
J2: IPBT-102-H1-T-S-RA-K; IPBT102H1TSRAK; Mouser Part Number 200-IPBT102H1TSRAK
J3: PET-02-01-T-VT-LC; SAMTEC_PET-02-XX-X-VT-LC; PARTREV C
K1: S82405VHR

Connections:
GND: D1.2 (A), J2.2, K1.2 (-)
unnamed: D1.1 (K), J2.1, K1.1 (+)
unnamed: J1.1, K1.3 (NC)
unnamed: J1.2, J3.1
unnamed: J3.2, K1.4 (NC)

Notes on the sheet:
Resistor Connector
12V Connector/Relay Control
HV Connector
